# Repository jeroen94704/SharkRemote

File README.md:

SharkRemote
===========

The goal of this project is to convert an AirSwimmer (http://www.airswimmers.com) helium balloon fish into to be controllable over a network. This is done by replacing the analog wireless control module with a n RFM12B wireless module controlled by an Atmega328 microcontroller. A base station in the form of a Nanode networked Arduino clone acts as a gateway between the RFM12B connection and the network. It provides a REST-like interface which can be used to control the AirSwimmer. 

RF12_Server
-----------

RF12_Client
-----------

REST interface
--------------

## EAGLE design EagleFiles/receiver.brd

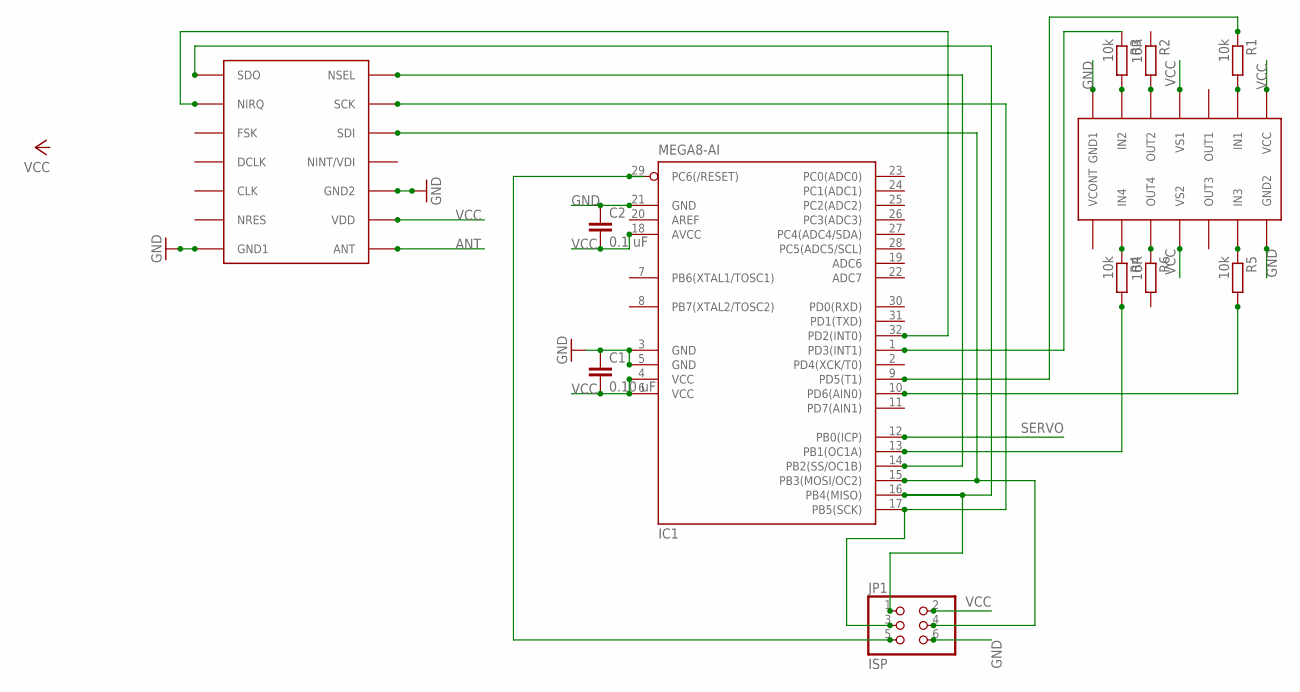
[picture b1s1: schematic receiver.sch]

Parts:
C1: 0.10 uF; C0805
C2: 0.1 uF; C0805
IC1: MEGA8-AI; TQFP32-08
JP1: ISP; 2X03
LB1836M: LB1836M; MFP-14
R1, R3, R4, R5: 10k; R2012
R2, R6: 10R; R2012
RFM12B: RFM12B

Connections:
ANT: RFM12B.ANT
GND: C1.1, C2.1, IC1.3 (GND), IC1.5 (GND), IC1.21 (GND), JP1.6, LB1836M.GN2 (GND2), LB1836M.GND1, RFM12B.GND1, RFM12B.GND2
unnamed: IC1.16 (PB4(MISO)), JP1.1, RFM12B.SDO
unnamed: IC1.15 (PB3(MOSI/OC2)), JP1.4, RFM12B.SDI
unnamed: IC1.17 (PB5(SCK)), JP1.3, RFM12B.SCK
unnamed: IC1.14 (PB2(SS/OC1B)), RFM12B.NSEL
unnamed: IC1.32 (PD2(INT0)), RFM12B.NIRQ
unnamed: LB1836M.IN1, R1.2
unnamed: IC1.9 (PD5(T1)), R1.1
unnamed: LB1836M.IN2, R3.2
unnamed: LB1836M.IN4, R4.1
unnamed: LB1836M.IN3, R5.1
unnamed: IC1.1 (PD3(INT1)), R3.1
unnamed: IC1.13 (PB1(OC1A)), R4.2
unnamed: IC1.10 (PD6(AIN0)), R5.2
unnamed: LB1836M.OUT2, R2.2
unnamed: LB1836M.OUT4, R6.1
unnamed: IC1.29 (PC6(/RESET)), JP1.5
SERVO: IC1.12 (PB0(ICP))
VCC: C1.2, C2.2, IC1.4 (VCC), IC1.6 (VCC), IC1.18 (AVCC), JP1.2, LB1836M.VCC, LB1836M.VS1, LB1836M.VS2, RFM12B.VDD

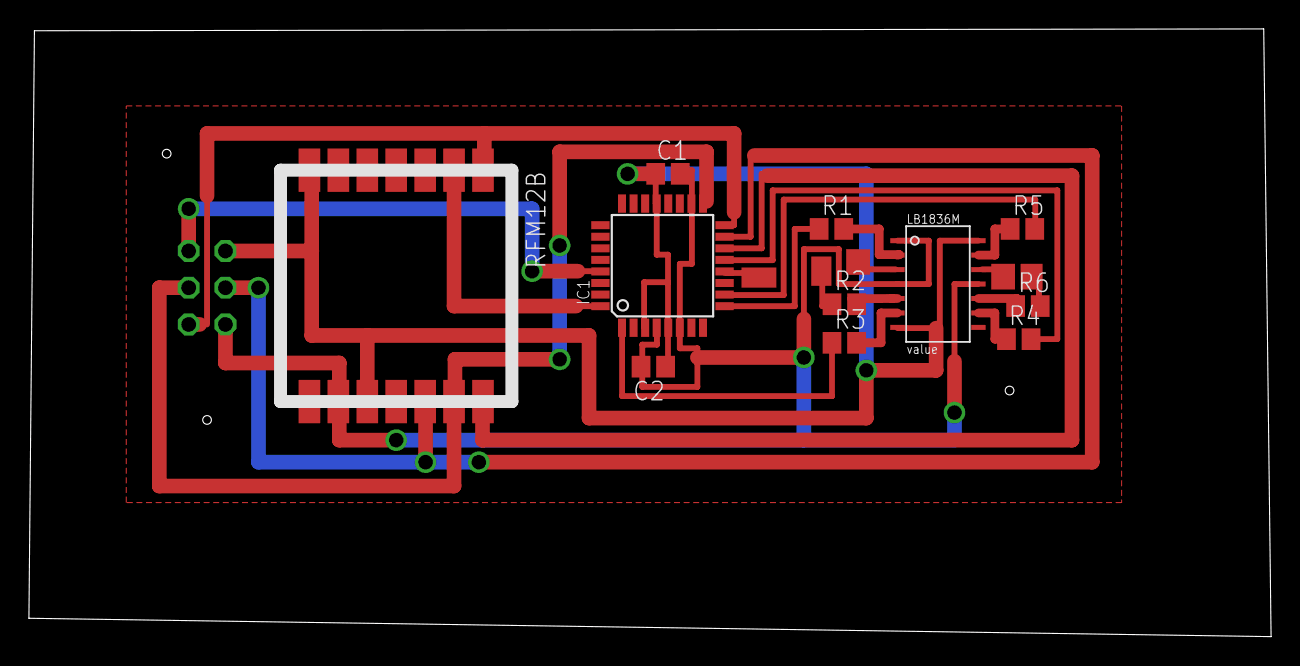
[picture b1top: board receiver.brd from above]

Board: 2 copper layers, 85.9 x 42.0 mm, 12 parts (1 on the bottom side), 18 nets.

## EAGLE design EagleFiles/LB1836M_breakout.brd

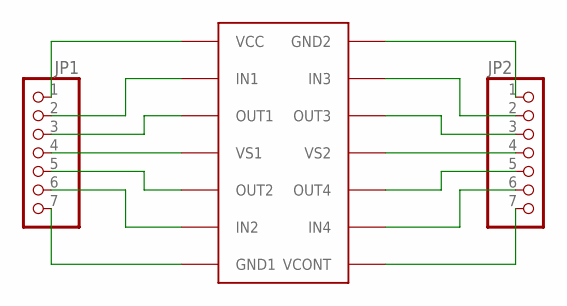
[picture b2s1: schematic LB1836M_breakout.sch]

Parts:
JP1, JP2: PINHD-1X7; 1X07
LB1836M: LB1836M; MFP-14

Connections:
unnamed: JP2.1, LB1836M.GN2 (GND2)
unnamed: JP2.2, LB1836M.IN3
unnamed: JP2.3, LB1836M.OUT3
unnamed: JP2.4, LB1836M.VS2
unnamed: JP2.5, LB1836M.OUT4
unnamed: JP2.6, LB1836M.IN4
unnamed: JP2.7, LB1836M.VCONT
unnamed: JP1.1, LB1836M.VCC
unnamed: JP1.2, LB1836M.IN1
unnamed: JP1.3, LB1836M.OUT1
unnamed: JP1.4, LB1836M.VS1
unnamed: JP1.5, LB1836M.OUT2
unnamed: JP1.6, LB1836M.IN2
unnamed: JP1.7, LB1836M.GND1

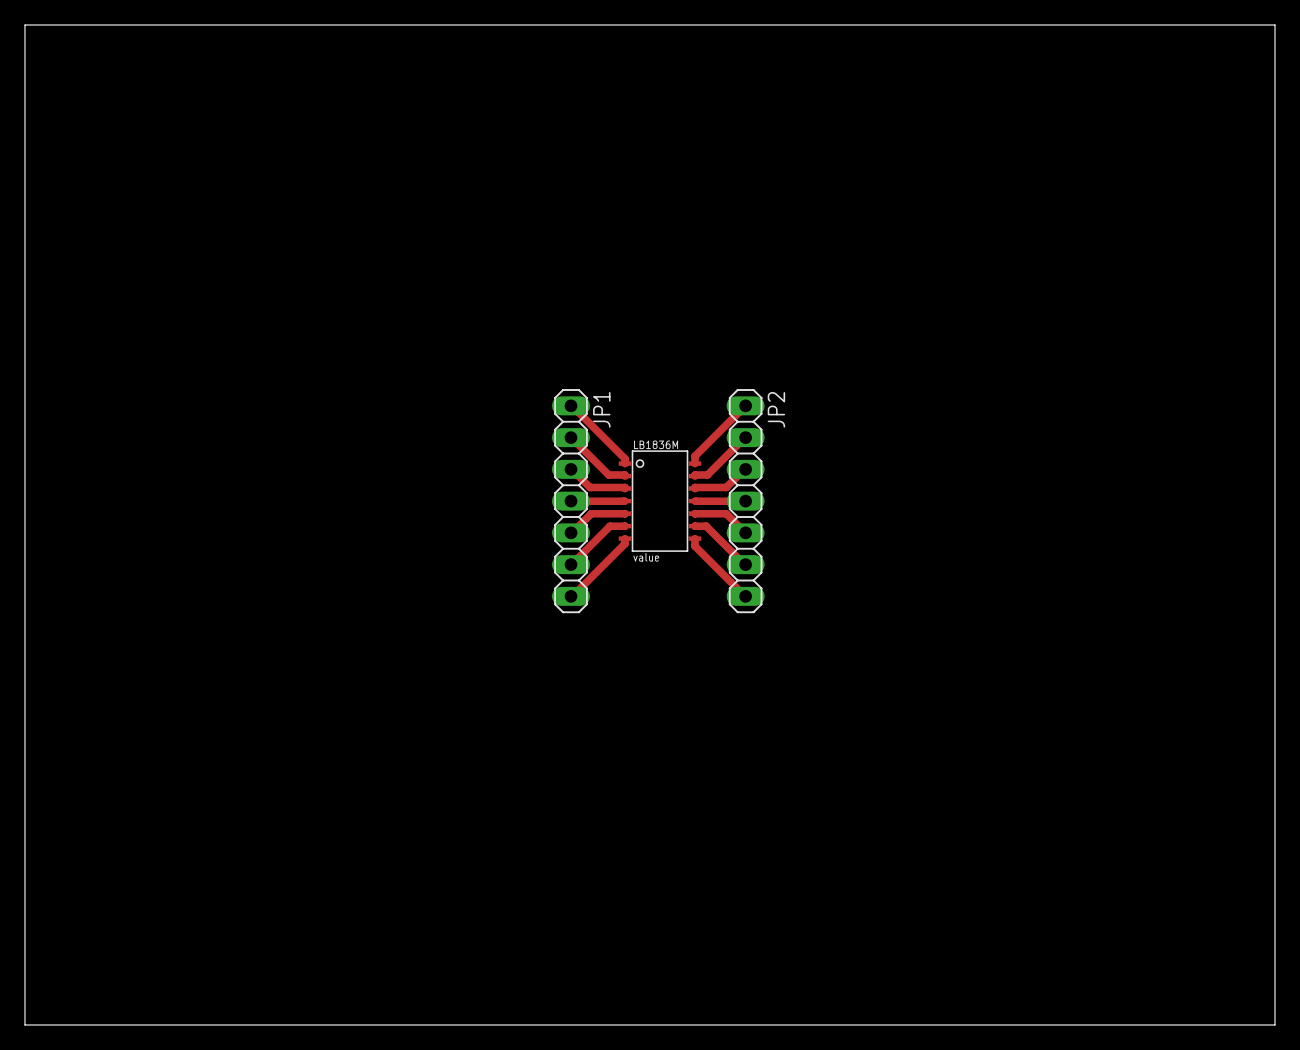
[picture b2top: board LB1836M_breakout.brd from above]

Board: 2 copper layers, 100.0 x 80.0 mm, 3 parts (0 on the bottom side), 14 nets.

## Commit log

2012-10-30 Added client and server code
2012-10-30 Updates to the readme
2013-04-01 Now controlling the tail fin over wireless
2013-04-21 Added eagle files for LB1836M breakout board and unfinished receiver
2013-05-14 Added test code for wireless comms
2013-08-13 made a change
2013-08-13 made a change to client section
2013-08-14 Added more stuff to the client section
2013-08-14 Adding more
2013-08-14 Added something about REST api
2013-08-14 Writing about the server
2013-08-14 Further development of the software
2013-08-15 Reorganized the repo a little bit. Keeping the RF12 dirs for now, but will probably get rid of those later
2013-08-15 Got rid of RFM12 stuff on main. It's still in rfm12experiments branch
2013-08-17 Working version of the REST-like API in the groundcontroller
2013-08-17 Merged changes from origin and removed file
2013-08-18 All REST commands now functional and processed correctly. Both on-board controller and ground station software now essentially feature complete
2014-02-25 Further development of the schematic and board
    Schematic finalized, added a pinheader for programming and corrected
    wiring errors. Board largely designed, including pads to solder the
    motor and servo wires to.
2014-04-15 Added openscad models
2014-04-15 Further development of software and board
    * Removed twitter publishing of ip address
    * Added on-board voltage monitoring
    * Small changes to receiver board.
2014-04-15 Small changes to board
2014-06-11 Added android control app
    - The android controil app is provided as an Android Studio project
    - Switched to a static IP for the ground station, at least for now.
    - Modified the PCB holder stl model
